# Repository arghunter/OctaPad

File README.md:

# OctoPad
An irregular octagon macropad. Why? I felt like it. 
## Features
- 1x OLED Screen
- 2x Rotary Encoders
- 4x MX Switches
- 16x Neopixel for Underglow

## BOM
- Seeed XIAO RP2040
- 4x MX-Style switches
- 2x EC11 Rotary encoders
- 1x 0.91 inch OLED displays
- 4x Blank DSA keycaps (White)
- 16x SK6812 MINI-E LEDs 

## Assembly

## PCB

## Case
- Stuck together with superglue

## Firmware
- Written in KMK within firmware folder.
- Mostly assorted Key Presses and a Screenshot button

## Extra Stuff
- May want to incorporate timer functionality with the neopixels as a completition ring later.

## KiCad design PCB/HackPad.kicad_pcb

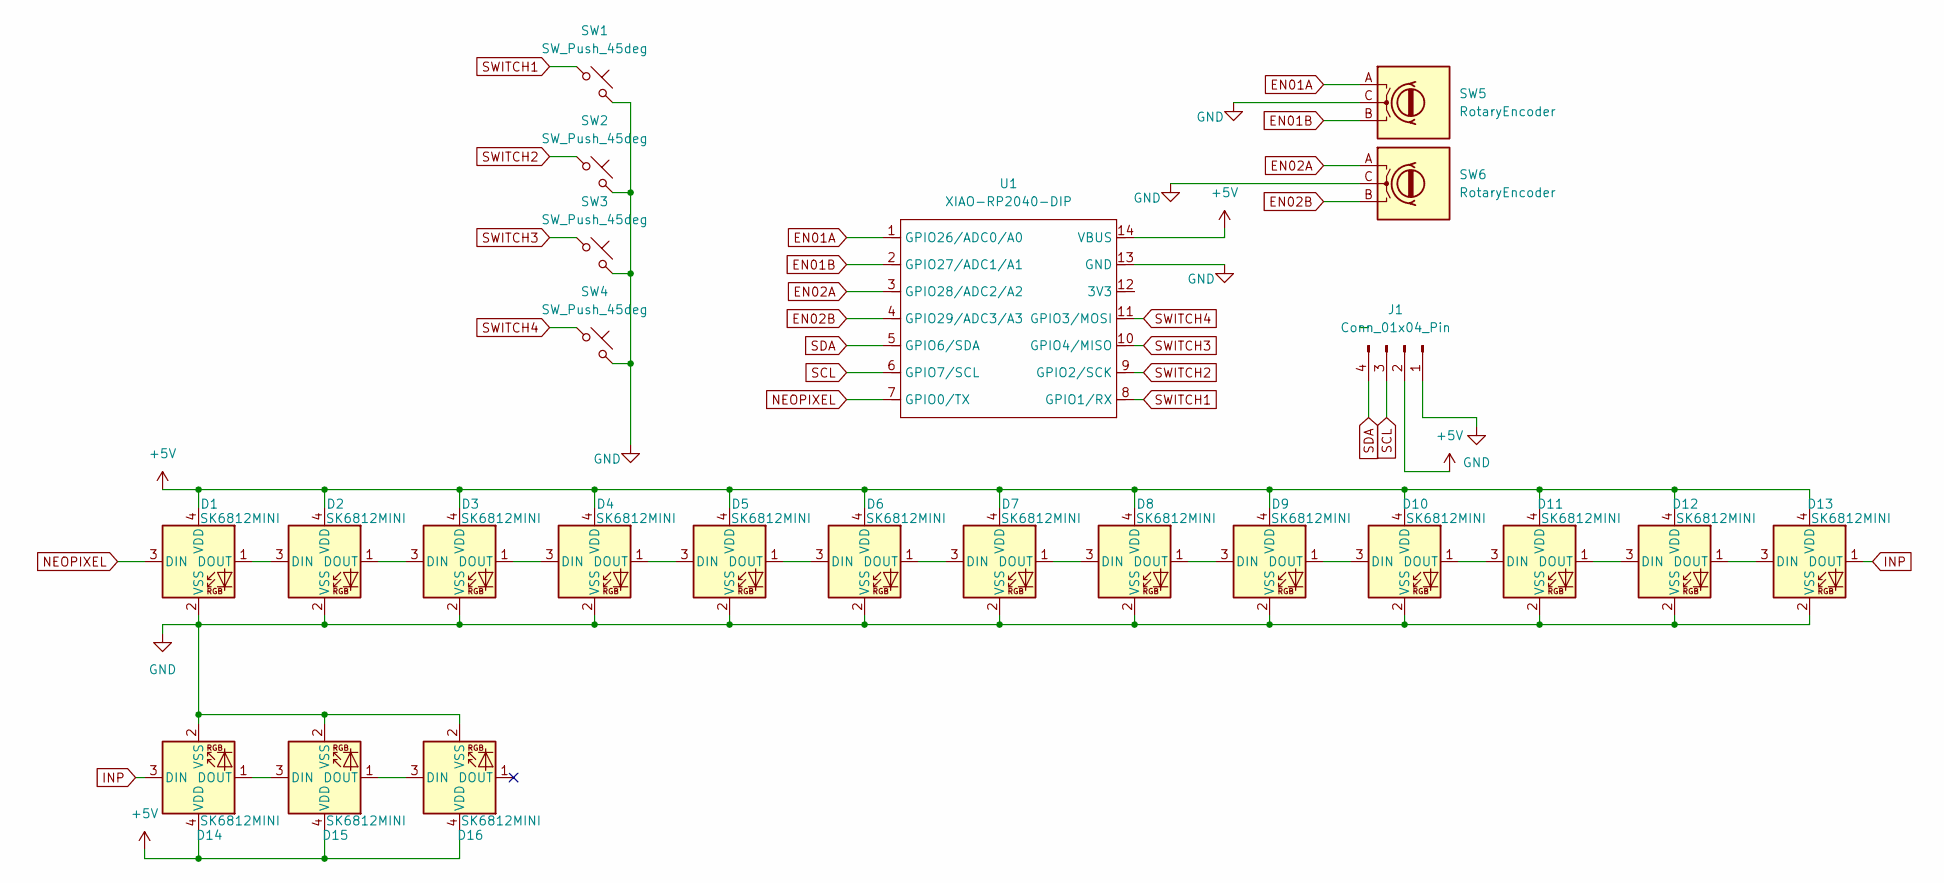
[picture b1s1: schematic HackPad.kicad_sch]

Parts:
D1, D2, D3, D4, D5, D6, D7, D8, D9, D10, D11, D12, D13, D14, D15, D16: SK6812MINI; LED_SK6812MINI_PLCC4_3.5x3.5mm_P1.75mm
J1: Conn_01x04_Pin; SSD1306-0.91-OLED-4pin-128x32
SW1, SW2, SW3, SW4: SW_Push_45deg; SW_Cherry_MX_1.00u_PCB
SW5, SW6: RotaryEncoder; RotaryEncoder_Alps_EC11E_Vertical_H20mm
U1: XIAO-RP2040-DIP

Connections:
+5V: D1.4 (VDD), D2.4 (VDD), D3.4 (VDD), D4.4 (VDD), D5.4 (VDD), D6.4 (VDD), D7.4 (VDD), D8.4 (VDD), D9.4 (VDD), D10.4 (VDD), D11.4 (VDD), D12.4 (VDD), D13.4 (VDD), D14.4 (VDD), D15.4 (VDD), D16.4 (VDD), J1.2, U1.14 (VBUS)
EN01A: SW5.A, U1.1 (GPIO26/ADC0/A0)
EN01B: SW5.B, U1.2 (GPIO27/ADC1/A1)
EN02A: SW6.A, U1.3 (GPIO28/ADC2/A2)
EN02B: SW6.B, U1.4 (GPIO29/ADC3/A3)
GND: D1.2 (VSS), D2.2 (VSS), D3.2 (VSS), D4.2 (VSS), D5.2 (VSS), D6.2 (VSS), D7.2 (VSS), D8.2 (VSS), D9.2 (VSS), D10.2 (VSS), D11.2 (VSS), D12.2 (VSS), D13.2 (VSS), D14.2 (VSS), D15.2 (VSS), D16.2 (VSS), J1.1, SW1.2, SW2.2, SW3.2, SW4.2, SW5.C, SW6.C, U1.13 (GND)
INP: D13.1 (DOUT), D14.3 (DIN)
NEOPIXEL: D1.3 (DIN), U1.7 (GPIO0/TX)
unnamed: D1.1 (DOUT), D2.3 (DIN)
unnamed: D2.1 (DOUT), D3.3 (DIN)
unnamed: D3.1 (DOUT), D4.3 (DIN)
unnamed: D4.1 (DOUT), D5.3 (DIN)
unnamed: D5.1 (DOUT), D6.3 (DIN)
unnamed: D6.1 (DOUT), D7.3 (DIN)
unnamed: D7.1 (DOUT), D8.3 (DIN)
unnamed: D8.1 (DOUT), D9.3 (DIN)
unnamed: D9.1 (DOUT), D10.3 (DIN)
unnamed: D10.1 (DOUT), D11.3 (DIN)
unnamed: D11.1 (DOUT), D12.3 (DIN)
unnamed: D12.1 (DOUT), D13.3 (DIN)
unnamed: D14.1 (DOUT), D15.3 (DIN)
unnamed: D15.1 (DOUT), D16.3 (DIN)
SCL: J1.3, U1.6 (GPIO7/SCL)
SDA: J1.4, U1.5 (GPIO6/SDA)
SWITCH1: SW1.1, U1.8 (GPIO1/RX)
SWITCH2: SW2.1, U1.9 (GPIO2/SCK)
SWITCH3: SW3.1, U1.10 (GPIO4/MISO)
SWITCH4: SW4.1, U1.11 (GPIO3/MOSI)

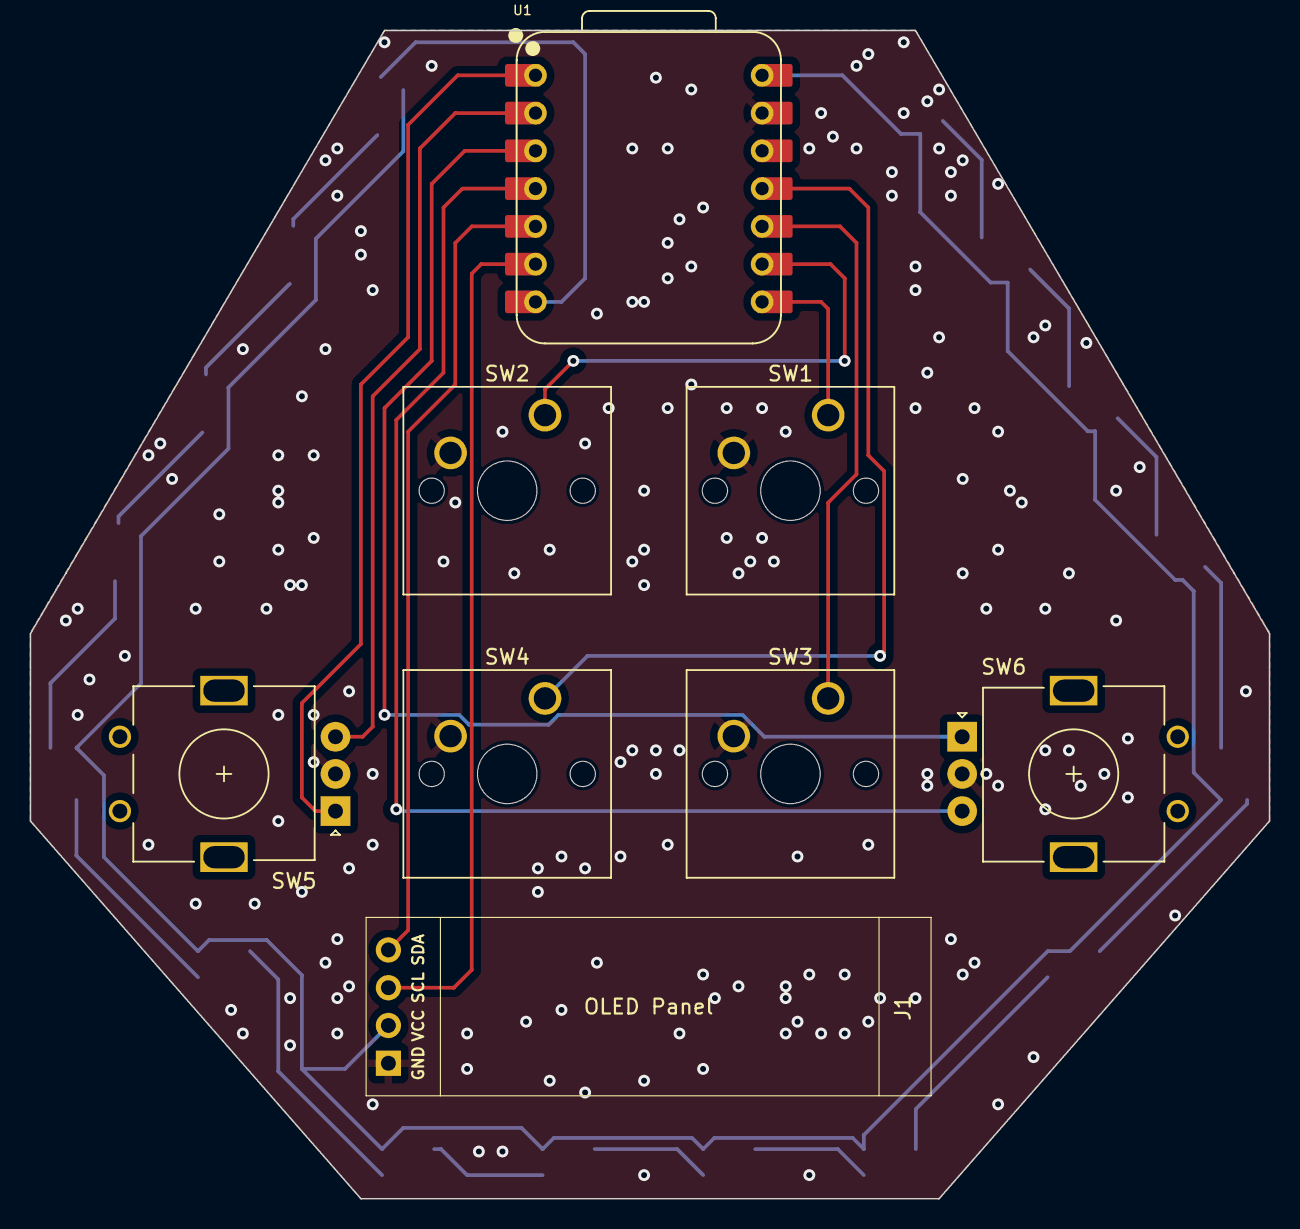
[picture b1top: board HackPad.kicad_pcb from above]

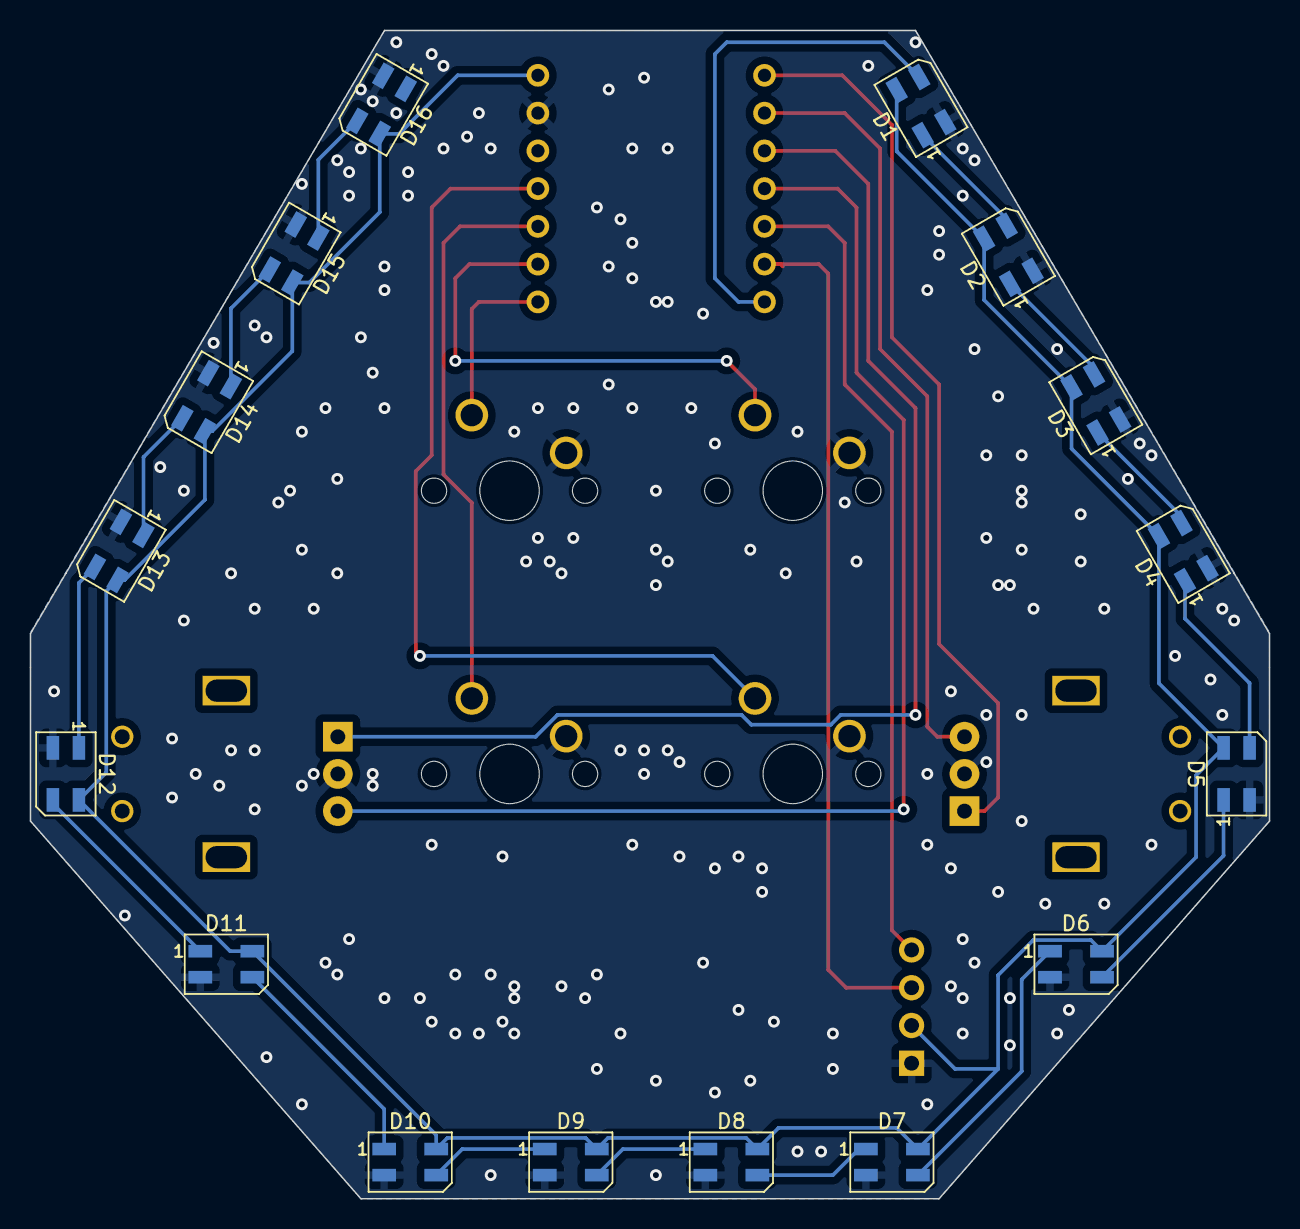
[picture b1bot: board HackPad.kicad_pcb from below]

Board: 2 copper layers, 83.3 x 78.6 mm, 24 parts (16 on the bottom side), 28 nets.

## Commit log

2025-06-15 upload
2025-06-16 production files
